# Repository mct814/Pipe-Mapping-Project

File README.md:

# Pipe-Mapping-Project

## Executive Summary
The problem that we wish to solve is a simple one. Underground PVC piping is often necessary to fix but difficult to locate. Methods currently exist for the detection of large industrial pipes, but there is a distinct lack of such technology for small, residential PVC
pipes. This project proposes a new way of mapping pipe networks by using a small probe to record positional data
while harmlessly traversing the pipe. The team’s objective is to create a probe based system to traverse and map variable sized underground pipe networks in 3D space, within an acceptable margin of error. While developing a mechanical pipe traversal method for the probe is part of this project, the primary goal consists of setting up the base technology for 3D mapping and real time information collection inside of 2"-4" PVC pipe.

## Current Version Capabilities
The current version of our design is still in the testing phase. While we have developed a functional testing system including a probe casing, pulley system and PVC network our current probe cannot fit inside the PVC pipe. The probe is using an arduino nano to pole data points and connect to the laptop which runs the mapping software. This probe can collect data while being powered by a set of 3 AA batteries and transmit said data to the PC. We have designed an improved system that would fit inside the 2" pipe but we have not yet implemented it. Our current mapping software can get data points within a relativiely similar shape to the physical path but still has a large margin of error. Further develpment of the mapping software is required to get within our original specification of 1" margin of error.

## Salient Outcomes
Our main successes came in the form of the mechanical testing system shown below and the preliminary maps created during testing.
* [Mechanical Testing](https://youtube.com/shorts/g99_hG3kM2Y?feature=share)

## Testing Video
* [Probe Testing](https://youtube.com/shorts/lbEazcovoQ8?feature=share)

## Project Photos

## About Us

### Developers

#### Adison Heathcott
I am a computer engineering senior at Tennessee Technological University. I am originally from Knoxville, TN and graduated from Bearden High School.

#### Ben Ask
I am a computer engineering senior at Tennessee Technological University. I am originally from Greensboro, NC and graduated from Ravenwood High School.

#### Caleb Thorne
I am an electrical engineering senior at Tennessee Technological University. I am originally from Pulaski, TN and graduated from Giles County High School.

#### Elizabeth Russell
I am an electrical engineering senior at Tennessee Technological University. I am originally from Tullahoma, TN and graduated from Family Christian Academy.

### Faculty Supervisor

#### Jesse Roberts

### Customer

#### Pipe locating services

## Description of Repository
The main file of the repository contains the lisence, readme, planned software file, reports folder, and project documentation folder. Inside of the reports folder are the original project proposal, the design phase 1 document, and the final report. Inside the project documentation folder is the bill of materials, project schematic and the folders for each of the subsystems that have been designed. Each of the subsystem folders contains schematics and readme descriptions of the design process.

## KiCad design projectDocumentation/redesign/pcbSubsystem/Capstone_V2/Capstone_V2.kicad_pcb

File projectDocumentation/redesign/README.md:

# Redesign

The redesigned PCB is listed under the pcbSubsystem folder. 

## Signoff

This signoff is for the redesign of the pipe mapping drone. It includes the PCB, 2 LDOs, and a new memory chip. 

Components 

5V LDO (link here) 

1.8V LDO (link here) 

Memory (link here) 

GPIO Jumper (link here) 

Each of the components are shown to fit our design and our constraints In previous sign off requests. The 5V LDO is identical to the 1.8V LDO but the output voltage is changed to be able to power the Arduino. 

The new PCB does not meet our previous constraints listed in the previous design documents, however, it does fit the new constraints and will fit on top of the Arduino. We are printing a new casing to fit the arduino as well.  

5V LDO constraints: 

Power constraint 

The LDO is rated on the datasheet to be able to supply an adequate amount of power to the Arduino nano and the 3V LDO.  

The remaining analysis is shown in the image at the bottom of the page. 

PCB constraints: 

Size constraint 

The PCB must be 43.2 mm in length and 18 mm in width. This new PCB design fits this constraint. 

The PCB must fit the Arduino Nano GPIO pins. This new PCB uses the Arduino Nano sizing schematic, and the Eagle files to check against, to ensure that the GPIO pin holes are in the correct location. 

Power constraint 

The PCB has the soldering points to be able to connect to the battery and is connected to the Arduino 5V and GND pins, after the LDO, to be able to power the Arduino as well.

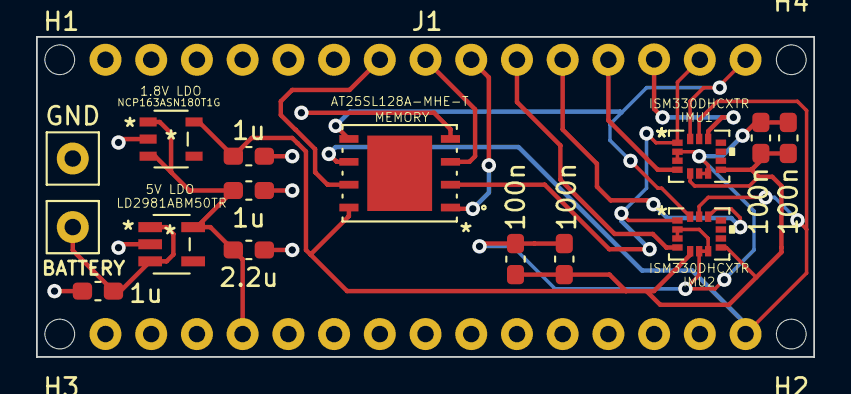
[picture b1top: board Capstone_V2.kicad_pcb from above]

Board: 2 copper layers, 43.2 x 17.8 mm, 21 parts (0 on the bottom side), 15 nets.

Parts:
1.8V LDO: NCP163ASN180T1G
1u, 1u#2, 1u#3: 1u; C_0603_1608Metric_Pad1.08x0.95mm_HandSolder
2.2u: 2.2u; C_0603_1608Metric_Pad1.08x0.95mm_HandSolder
5V LDO: LD2981ABM50TR
100n, 100n#2, 100n#3, 100n#4: 100n; C_0603_1608Metric_Pad1.08x0.95mm_HandSolder
BATTERY: TestPoint; TestPoint_THTPad_2.5x2.5mm_Drill1.2mm
GND: TestPoint; TestPoint_THTPad_2.5x2.5mm_Drill1.2mm
H1, H2, H3, H4: MountingHole; MountingHole_2.1mm
IMU1, IMU2: ISM330DHCXTR
J1, J2: Conn_01x15; Molex_KK-254_AE-6410-15A_1x15_P2.54mm_Vertical
MEMORY: AT25SL128A-MHE-T

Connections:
1.8 V: 1.8V LDO.5 (OUT), 1u.1, 100n.2, 100n#2.2, 100n#3.2, 100n#4.2, IMU1.5 (VDDIO), IMU1.8 (VDD), IMU2.5 (VDDIO), IMU2.8 (VDD), MEMORY.8 (VCC)
5 V IN: 1.8V LDO.1 (IN), 1.8V LDO.3 (EN), 1u#2.1, 2.2u.1, 5V LDO.5 (VOUT), J2.12
/RST: J1.3, J2.13
Battery: 1u#3.1, 5V LDO.1 (VIN), 5V LDO.3 (INHIBIT), BATTERY.1
GND: 1.8V LDO.2 (GND), 1u.2, 1u#2.2, 1u#3.2, 2.2u.2, 5V LDO.2 (GND), 100n.1, 100n#2.1, 100n#3.1, 100n#4.1, GND.1, IMU1.2 (SDx), IMU1.3 (SCx), IMU1.6 (GND), IMU1.7 (GND), IMU2.2 (SDx), IMU2.3 (SCx), IMU2.6 (GND), IMU2.7 (GND), J1.4, J2.14, MEMORY.4 (GND)
HOLD PIN: J1.7, MEMORY.7 (*HOLDIO3)
IMU1 CS PIN: IMU1.12 (CS), J1.13
IMU1 INT1 PIN: IMU1.4 (INT1), J1.12
IMU2 CS PIN: IMU2.12 (CS), J1.11
IMU2 INT1 PIN: IMU2.4 (INT1), J1.10
MEM CS PIN: J1.9, MEMORY.1 (*CS)
SPI CLK: IMU1.13 (SCL), IMU2.13 (SCL), J2.1, MEMORY.6 (SCK)
SPI MISO: IMU1.14 (SDA), IMU2.14 (SDA), J1.15, MEMORY.5 (SIIO0)
SPI MOSI: IMU1.1 (SDO/SA0), IMU2.1 (SDO/SA0), J1.14, MEMORY.2 (SOIO1)
WP PIN: J1.8, MEMORY.3 (*WPIO2)

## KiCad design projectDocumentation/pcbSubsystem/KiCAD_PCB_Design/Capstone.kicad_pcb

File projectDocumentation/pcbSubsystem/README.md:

# PCB Subsystem

## PCB Schematic

## KiCAD Files
KiCad files are supplied and can be loaded into KiCAD.

***CAUTION***
*The current design has errors. Look to the redesign for error corrections and a usable PCB*

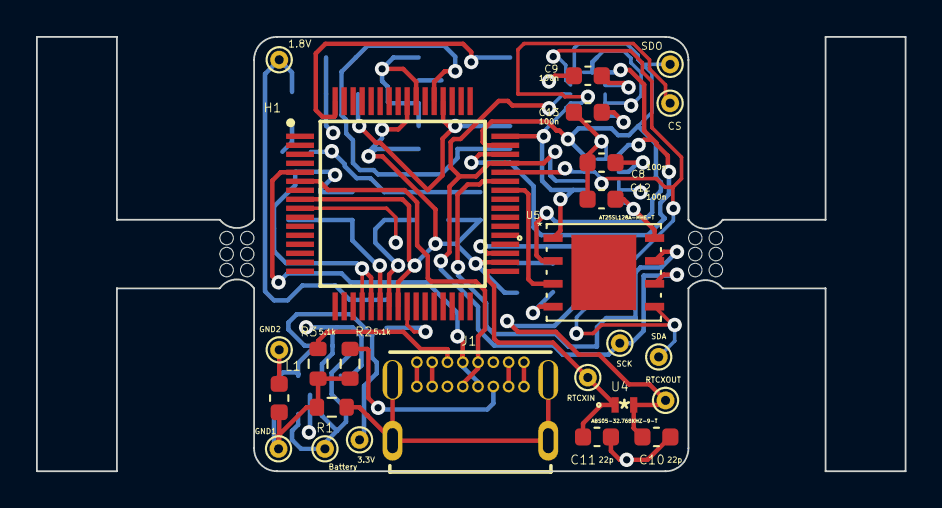
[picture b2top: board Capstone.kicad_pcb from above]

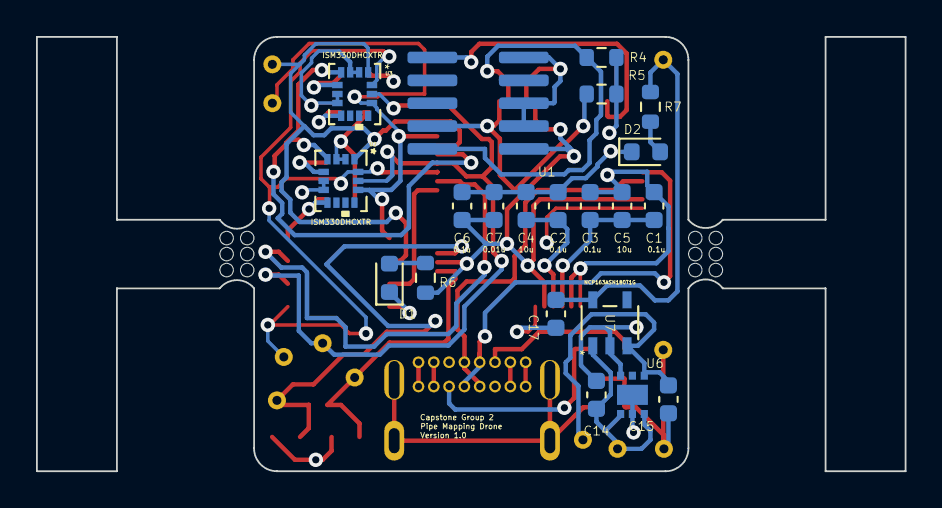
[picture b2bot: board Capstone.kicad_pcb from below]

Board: 4 copper layers, 48.3 x 24.1 mm, 50 parts (21 on the bottom side), 25 nets.

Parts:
1.8V, 3.3V: TestPoint; TestPoint_THTPad_D1.0mm_Drill0.5mm
 : MountingHole_2.1mm
 #2,  #3,  #4: MountingHole_2.1mm
Battery: TestPoint; TestPoint_THTPad_D1.0mm_Drill0.5mm
C1, C2, C3, C6: 0.1u; C_0603_1608Metric
C4, C5: 10u; C_0603_1608Metric
C7: 0.01u; C_0603_1608Metric
C8, C9, C12, C13: 100n; C_0603_1608Metric
C10, C11: 22p; C_0603_1608Metric
C14, C15, C17: 1u; C_0603_1608Metric
CS: TestPoint; TestPoint_THTPad_D1.0mm_Drill0.5mm
D1, D2: LED; LED_0603_1608Metric
GND1, GND2: TestPoint; TestPoint_THTPad_D1.0mm_Drill0.5mm
H1: LPC54113J128BD64QL; QFP50P1200X1200X160-64N
J1: USB4085-GF-A_REVA4; GCT_USB4085-GF-A_REVA4
L1: L; L_0603_1608Metric
R1, R6, R7: 1M; R_0603_1608Metric
R2, R3: 5.1k; R_0603_1608Metric
R4, R5: 10k; R_0603_1608Metric
RTCXIN: TestPoint; TestPoint_THTPad_D1.0mm_Drill0.5mm
RTCXOUT: TestPoint; TestPoint_THTPad_D1.0mm_Drill0.5mm
SCK: TestPoint; TestPoint_THTPad_D1.0mm_Drill0.5mm
SDA: TestPoint; TestPoint_THTPad_D1.0mm_Drill0.5mm
SDO: TestPoint; TestPoint_THTPad_D1.0mm_Drill0.5mm
U1: SWD_485-4048
U2, U3: ISM330DHCXTR
U4: ABS05-32.768KHZ-9-T
U5: AT25SL128A-MHE-T
U6: NCP730BMT330TBG
U7: NCP163ASN180T1G

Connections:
1.8V: 1.8V.1, C8.1, C9.1, C12.1, C13.1, C17.1, R7.1, U2.5 (VDDIO), U2.8 (VDD), U3.5 (VDDIO), U3.8 (VDD), U5.8 (VCC), U7.5 (OUT)
3.3V: 3.3V.1, C1.2, C2.1, C3.2, C4.1, C5.1, C6.1, C7.1, C15.1, H1.8 (VDD_1), H1.22 (VREFP), H1.23 (VDDA), H1.24 (VDD_2), H1.34 (VDD_3), H1.56 (VDD_4), R4.1, R5.1, R6.1, U1.1 (VCC), U6.1 (OUT), U7.3 (EN)
Battery: Battery.1, C14.1, U6.4 (EN), U6.6 (IN), U7.1 (IN)
GND1: C2.2, C4.2, C6.2, C7.2, C8.2, C9.2, C10.2, C11.2, C12.2, C13.2, C14.2, C15.2, C17.2, D1.1 (K), D2.1 (K), GND1.1, H1.9 (VSS_1), H1.25 (VSS_2), H1.55 (VSS_3), J1.A1 (GND), J1.A12 (GND), J1.B1 (GND), J1.B12 (GND), L1.1, R1.2, R2.2, R3.2, U1.3 (GND), U1.5 (GND), U1.9 (GND), U2.2 (SDx), U2.3 (SCx), U2.6 (GND), U2.7 (GND), U3.2 (SDx), U3.3 (SCx), U3.6 (GND), U3.7 (GND), U5.4 (GND), U6.3 (GND), U6.5 (NC/PG), U6.7 (EP), U7.2 (GND)
GND2: C1.1, C3.1, C5.2, GND2.1, H1.20 (VSSA), H1.21 (VREFN), L1.2
unnamed: C10.1, H1.35 (RTCXOUT), RTCXOUT.1, U4.2
unnamed: C11.1, H1.33 (RTCXIN), RTCXIN.1, U4.1
unnamed: D1.2 (A), R6.2
unnamed: D2.2 (A), R7.2
unnamed: H1.5 (USB_DP), J1.A6 (DP1), J1.B6 (DP2)
unnamed: H1.6 (USB_DM), J1.A7 (DN1), J1.B7 (DN2)
unnamed: H1.42 (PIO1_11), U5.3 (*WPIO2)
unnamed: H1.43 (PIO0_8), U5.7 (*HOLDIO3)
unnamed: H1.44 (PIO0_9), SDA.1, U2.14 (SDA), U3.14 (SDA), U5.5 (SIIO0)
unnamed: H1.45 (PIO0_10), SCK.1, U2.13 (SCL), U3.13 (SCL), U5.6 (SCK)
unnamed: H1.46 (PIO0_11), U2.4 (INT1), U3.4 (INT1)
unnamed: H1.47 (PIO0_12), SDO.1, U2.1 (SDO/SA0), U3.1 (SDO/SA0), U5.2 (SOIO1)
unnamed: CS.1, H1.48 (PIO0_13), U2.12 (CS), U3.12 (CS), U5.1 (*CS)
unnamed: H1.52 (SWCLK/PIO0_16), R5.2, U1.4 (SWDCLK)
unnamed: H1.53 (SWDIO/PIO0_17), R4.2, U1.2 (SWDIO)
unnamed: H1.64 (RESET), U1.10 (RESET)
unnamed: J1.A4 (VBUS), J1.A9 (VBUS), J1.B4 (VBUS), J1.B9 (VBUS)
unnamed: J1.A5 (CC1), R3.1
unnamed: J1.B5 (CC2), R2.1
unnamed: J1.P1 (SHELL), J1.P2 (SHELL), J1.P3 (SHELL), J1.P4 (SHELL), R1.1

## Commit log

2022-05-05 Microcontroller addition
2022-05-05 Quick fix
2022-05-05 Create Memory
2022-05-05 Mechanical Subsystem Addition
2022-05-05 Update Memory
2022-05-05 SolidWorks Added
2022-05-05 Create imu subsystem
2022-05-05 Added pictures and updated readme
2022-05-05 memory subsystem name
2022-05-05 Create Design phase 1
2022-05-06 Moved files
2022-05-06 Planned software addition
2022-09-17 Added BOM info
2022-11-08 Create pythonprogram
2022-11-08 Added memory experiment portion
2022-11-09 added graphs for experiment 1
2022-11-09 switched folder
2022-11-09 changed folder
2022-11-09 Fixed Memory Analysis
    A portion of the memory analysis was removed by a previous git commit. Fixed it.
2022-11-11 Updated Experimental Analysis
2022-11-20 Updated new experimentation
2022-11-29 Power Subsystem additions
2022-11-29 Added poster and final BOM
2022-11-29 Updated PCB and software
2022-11-29 moved some pics
2022-11-29 Updated software
2022-12-01 added motor controller subsystem and probe casing subsystem
2022-12-01 edited pictures
2022-12-01 added pictures
2022-12-01 changed picture location
2022-12-01 added image
2022-12-02 Moved lessons learned

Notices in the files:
parts and their libraries:
Copyright 2021 Accelerated Designs. All rights reserved.
